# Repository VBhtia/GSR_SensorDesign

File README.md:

# GSR Sensor Design

The complete circuit for Galvanic Skin Response Sensor consists of four stages :

1. Wheatstone Bridge 
2. Unity Buffer 
3. Differential Amplifier 
4. Low Pass Filter

| S.No | Item   | Value |
|------|--------|-------|
| 1    | R3, R4 | 10k   |
| 2    | RV1    | 50k   |
| 3    | R7, R8 | 1.3M  |
| 4    | R5, R6 | 100k  |

## Galvanic Skin Response (GSR) Sensor Design

This section explains the design and functioning of the GSR sensor circuit, which measures the electrical conductance of the skin. The conductance varies with the moisture level and is used to assess physiological arousal.

### Circuit Diagram

### Components

- **R1, R2, R3, R4, R5, R6, R7, R8, R9**: Resistors with appropriate values for the circuit.
- **RV1**: Variable resistor/potentiometer for calibration.
- **U1:A, U1:B, U1:C**: LM324 operational amplifiers used for signal amplification and processing.
- **C4**: Capacitor for filtering.
- **Electrodes**: Connected to the skin to measure conductance.

### Working Principle

1. **Electrode Placement**: Electrodes are placed on the skin to measure the electrical conductance.
2. **Signal Conditioning**: The conductance signal from the electrodes is conditioned using the operational amplifiers (U1:A, U1:B, U1:C). The signal is amplified and filtered to obtain a stable reading.
3. **Data Processing**: The processed signal is then sent to a microcontroller (µC) for further analysis and data logging.

### How to Use

1. **Calibration**: Adjust RV1 to calibrate the sensor for accurate readings.
2. **Electrode Placement**: Place the electrodes on the skin.
3. **Power Up**: Power the circuit and observe the output signal on the microcontroller.
4. **Data Logging**: Use the microcontroller to log the data for analysis.

This GSR sensor circuit can be integrated with the serial to Firebase data logger for real-time monitoring and analysis of physiological data.

## License

This project is licensed under the MIT License.

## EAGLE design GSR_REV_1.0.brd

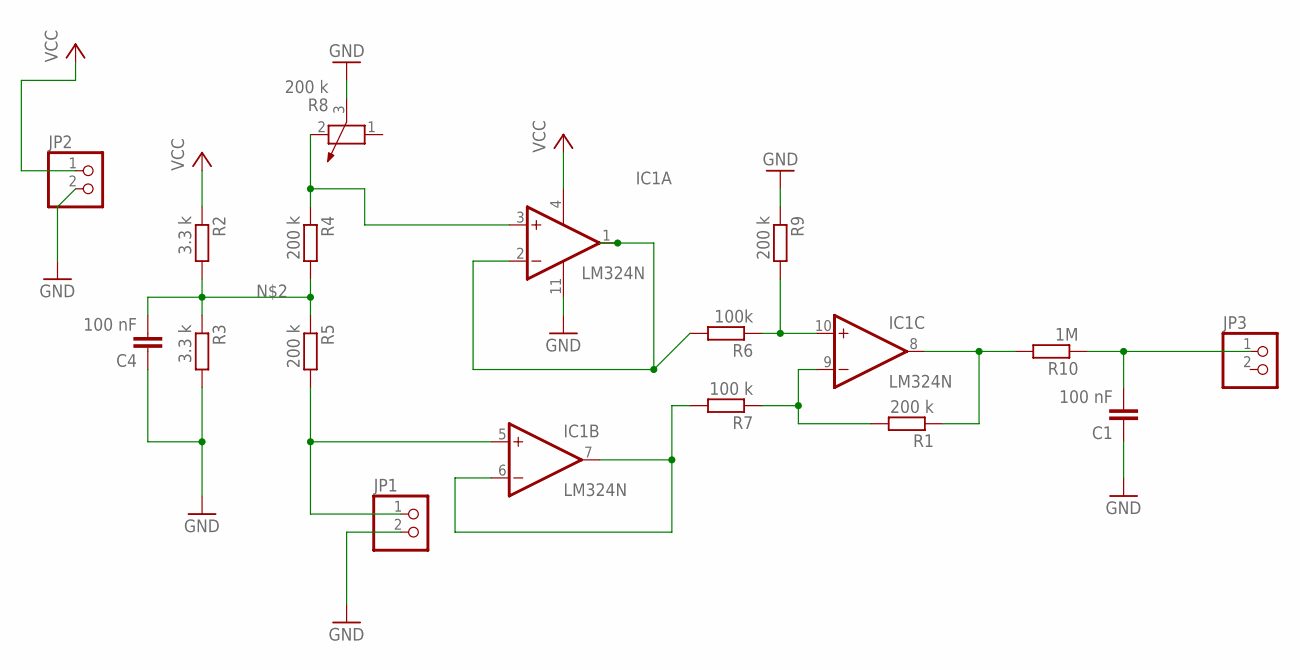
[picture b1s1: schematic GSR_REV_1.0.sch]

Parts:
C1, C4: 100 nF; C025-025X050
IC1: LM324N; DIL14
JP1, JP2, JP3: PINHD-1X2; 1X02
R1, R4, R5, R9: 200 k; 0207/12
R2, R3: 3.3 k; 0207/12
R6: 100k; 0207/12
R7: 100 k; 0207/12
R8: 200 k; PT-10
R10: 1M; 0207/12

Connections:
GND: C1.1, C4.1, IC1.11 (V-), JP1.2, JP2.2, R3.2, R8.3, R9.1
unnamed: C4.2, R2.2, R3.1, R4.2, R5.1
unnamed: IC1.3 (+IN), R4.1, R8.2
unnamed: IC1.6 (-IN), IC1.7 (OUT), R7.2
unnamed: IC1.5 (+IN), JP1.1, R5.2
unnamed: C1.2, JP3.1, R10.1
unnamed: IC1.10 (+IN), R6.1, R9.2
unnamed: IC1.9 (-IN), R1.2, R7.1
unnamed: IC1.8 (OUT), R1.1, R10.2
unnamed: IC1.1 (OUT), IC1.2 (-IN), R6.2
VCC: IC1.4 (V+), JP2.1, R2.1

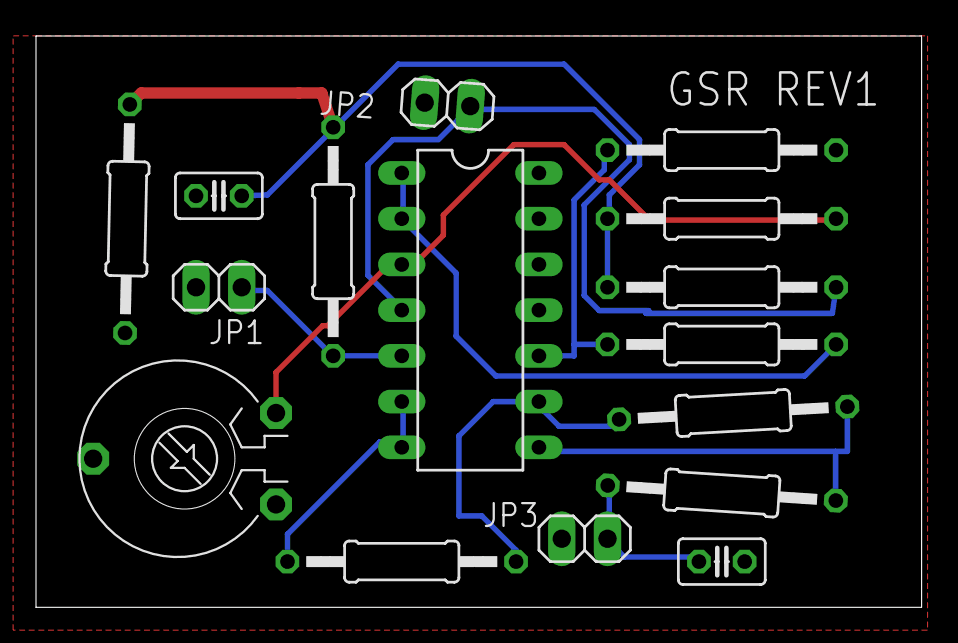
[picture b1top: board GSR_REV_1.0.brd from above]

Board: 2 copper layers, 49.2 x 31.7 mm, 16 parts (0 on the bottom side), 11 nets.

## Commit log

2020-01-25 Galvanic Skin Response Sensor Design Files
